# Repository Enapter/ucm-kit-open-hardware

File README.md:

# What is Enapter UCM Kit

This repository hosts Enapter UCM Kit open hardware documentation for building your own IoT edge devices. It is specially designed for makers, students and researchers to test, learn and teach IoT and Smart Energy.

Enapter UCM Kit based on several important open source and free to use components and provides full-stack IoT technology kit (hardware and software) for rapid development of connected appplications. This opens possibilities for personal technology trials and hardware prototyping. Which is extremely helpful for developing innovative cost-efficient smart energy solutions for emerging markets.

# How to Use

All schematics, CAD files and supplementary materials in this repository are subject of [Solderpad Hardware License v2.1](http://solderpad.org/licenses/SHL-2.1/). Feel free to modify and use for your own projects.

Find more information about Enapter UCM Kit at [Enapter Developer's Portal](https://go.enapter.com/ucmkit-enpkit).

# Release Notes

Check out the [Changelog](./CHANGELOG.md) for the latest updates and release notes.

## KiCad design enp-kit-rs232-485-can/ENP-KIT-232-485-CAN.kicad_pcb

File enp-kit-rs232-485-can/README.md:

## ENP-KIT-232-485-CAN

The ENP-KIT-232-485-CAN board is used for demonstrating the capabilities of the Enapter software, implements RS232, RS485, CAN interfaces.

Board was designed in an open-source EDA software <a href="https://www.kicad.org/" target="_blank">KiCad 6.0.</a>

| Description        | Resource                                                     | Note        |
| ------------------ | ------------------------------------------------------------ | ----------- |
| Production files   | [Full set of docs/files](./Production_files/ENP-KIT-232-485-CAN_V1.0.zip)| ZIP archive |
| Schematic          | [ENP-KIT-232-485-CAN](./Production_files/ENP-KIT-232-485-CAN_V1.0_schematic.pdf)  | PDF         |
| Quick Start Guide  | Coming soon... | PDF         |
| Plastic Enclosure  | <a href="https://www.budind.com/product/general-use-boxes/utilibox-style-j-series-utility-boxes/cu-1941-mb" target="_blank">CU-1941-MB</a> | Plastic box, suitable for this board |
| Where to order for production  | <a href="https://cart.jlcpcb.com/quote?orderType=1&stencilLayer=2&stencilWidth=100&stencilLength=100" target="_blank">jlcpcb.com</a> | You can order the board together with SMT Assembly, there is a separate [archive](./Production_files/jlcpcb_files_V1.0.zip) that includes everything you need |

You also need module:
ESP32-DevKitC-32D and micro USB - USB cable.

Be careful these components are not in the BOM.

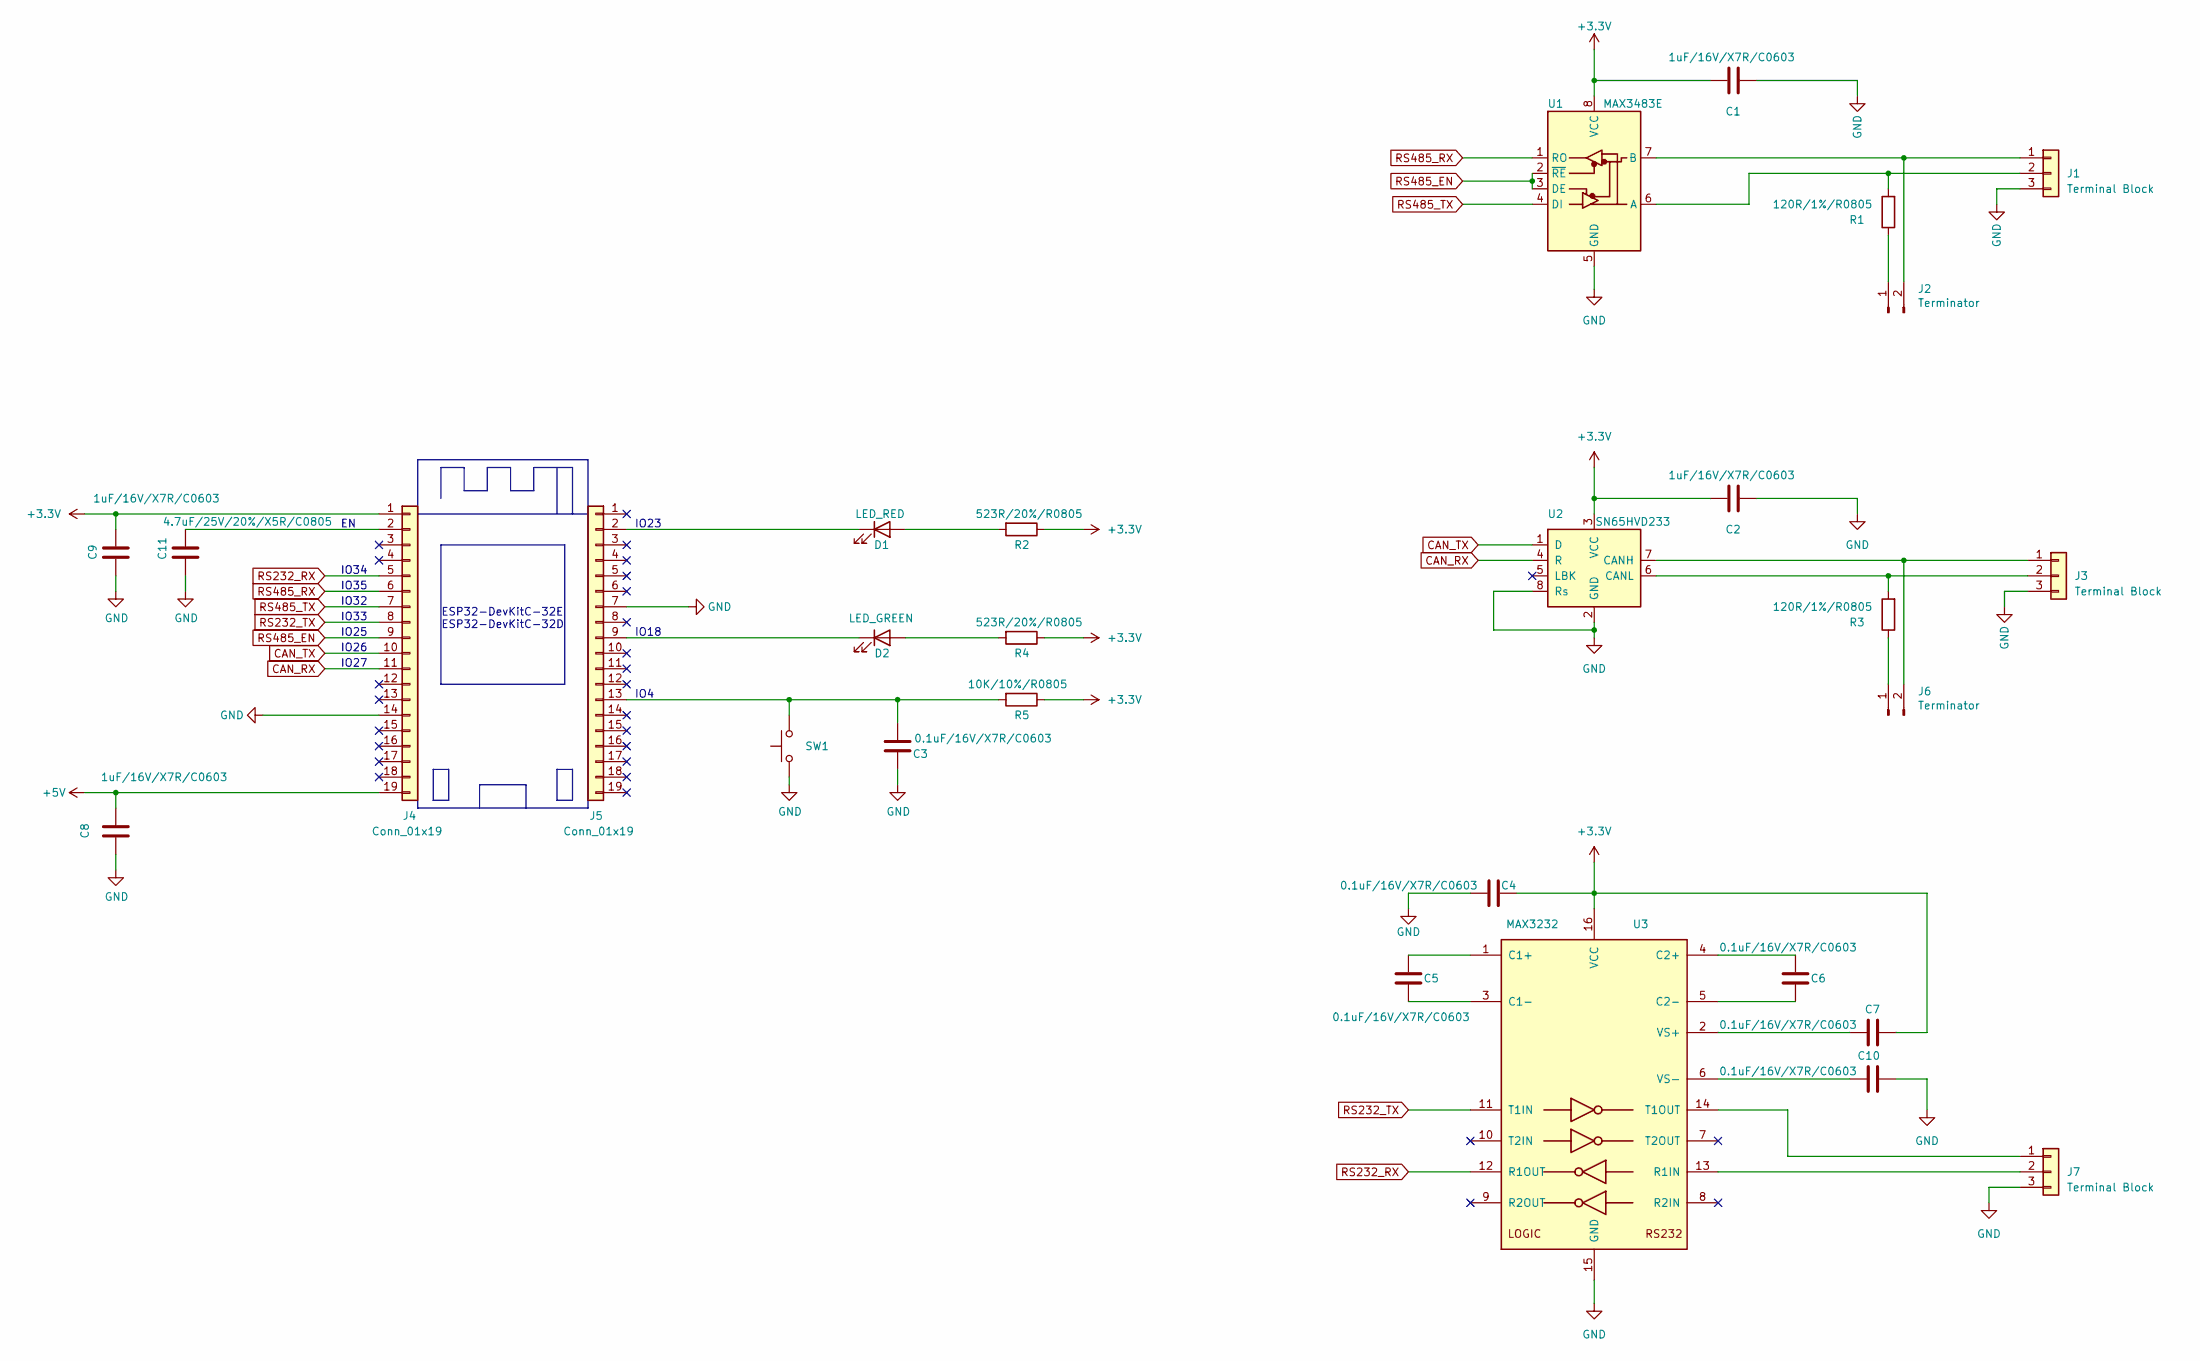
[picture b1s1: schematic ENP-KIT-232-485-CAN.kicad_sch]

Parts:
C1, C2, C8, C9: 1uF/16V/X7R/C0603; C_0603_1608Metric; Part number CL10A105KB8NNNC; JLCPCB Part # C15849
C3, C4, C5, C6, C7, C10: 0.1uF/16V/X7R/C0603; C_0603_1608Metric; Part number CC0603KRX7R9BB104; JLCPCB Part # C14663
C11: 4.7uF/25V/20%/X5R/C0805; C_0805_2012Metric; Part number CL21A475KAQNNNG; JLCPCB Part # C1779
D1: LED_RED; LED_0805_2012Metric; Part number APT2012SURC; JLCPCB Part # C84256
D2: LED_GREEN; LED_0805_2012Metric; Part number APT2012ZGC; JLCPCB Part # C2297
J1, J3, J7: Terminal Block; TerminalBlock_Phoenix_PT-1,5-3-3.5-H_1x03_P3.50mm_Horizontal; Part number DG350-3.5-03P-14-00A(H); JLCPCB Part # C2760669
J2, J6: Terminator; PinHeader_1x02_P2.54mm_Vertical; Part number DS1021-1*2SF11-B; JLCPCB Part # C492401
J4, J5: Conn_01x19; PinSocket_1x19_P2.54mm_Vertical; Part number PBS-19 (DS1023-1*19SF1); JLCPCB Part # C319202
R1, R3: 120R/1%/R0805; R_0805_2012Metric; Part number RC0805FR-07120RL; JLCPCB Part # C114245
R2, R4: 523R/20%/R0805; R_0805_2012Metric; Part number RC0805FR-07523RL; JLCPCB Part # C218615
R5: 10K/10%/R0805; R_0805_2012Metric; Part number RC0805FR-0710KL; JLCPCB Part # C17414
SW1: SW_Push; SW_Push_1P1T_NO_6x6mm_H9.5mm; Part number DTSM-62Y-V-T/R; JLCPCB Part # C2834922
U1: MAX3483E; SO-8_3.9x4.9mm_P1.27mm; Part number MAX3485EESA+; JLCPCB Part # C668204
U2: SN65HVD233; SOIC-8_3.9x4.9mm_P1.27mm; Part number SN65HVD231DR; JLCPCB Part # C129257
U3: MAX3232; SOIC-16_3.9x9.9mm_P1.27mm; Part number MAX3232ESE+; JLCPCB Part # C2904738

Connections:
+3.3V: C1.1, C2.1, C4.2, C7.2, C9.1, J4.1, R2.1, R4.1, R5.1, U1.8 (VCC), U2.3 (VCC), U3.16 (VCC)
+5V: C8.1, J4.19; also elsewhere on the board
CAN_RX: J4.11, U2.4 (R)
CAN_TX: J4.10, U2.1 (D)
GND: C1.2, C2.2, C3.1, C4.1, C8.2, C9.2, C10.2, C11.2, J1.3, J3.3, J4.14, J5.7, J7.3, SW1.1, U1.5 (GND), U2.2 (GND), U2.8 (Rs), U3.15 (GND); also elsewhere on the board
unnamed: C3.2, J5.13, R5.2, SW1.2
unnamed: C5.1, U3.3 (C1-)
unnamed: C5.2, U3.1 (C1+)
unnamed: C6.1, U3.5 (C2-)
unnamed: C6.2, U3.4 (C2+)
unnamed: C7.1, U3.2 (VS+)
unnamed: C10.1, U3.6 (VS-)
unnamed: D1.1 (K), J5.2
unnamed: D1.2 (A), R2.2
unnamed: D2.1 (K), J5.9
unnamed: D2.2 (A), R4.2
unnamed: J1.1, J2.2, U1.7 (B)
unnamed: J1.2, R1.2, U1.6 (A)
unnamed: J2.1, R1.1
unnamed: J3.1, J6.2, U2.7 (CANH)
unnamed: J3.2, R3.2, U2.6 (CANL)
unnamed: C11.1, J4.2
unnamed: J6.1, R3.1
unnamed: J7.1, U3.14 (T1OUT)
unnamed: J7.2, U3.13 (R1IN)
RS232_RX: J4.5, U3.12 (R1OUT)
RS232_TX: J4.8, U3.11 (T1IN)
RS485_EN: J4.9, U1.2 (~RE), U1.3 (DE)
RS485_RX: J4.6, U1.1 (RO)
RS485_TX: J4.7, U1.4 (DI)

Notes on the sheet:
IO4
IO35
IO26
IO27
IO18
ESP32-DevKitC-32E ESP32-DevKitC-32D
IO32
IO34
IO33
IO23
IO25

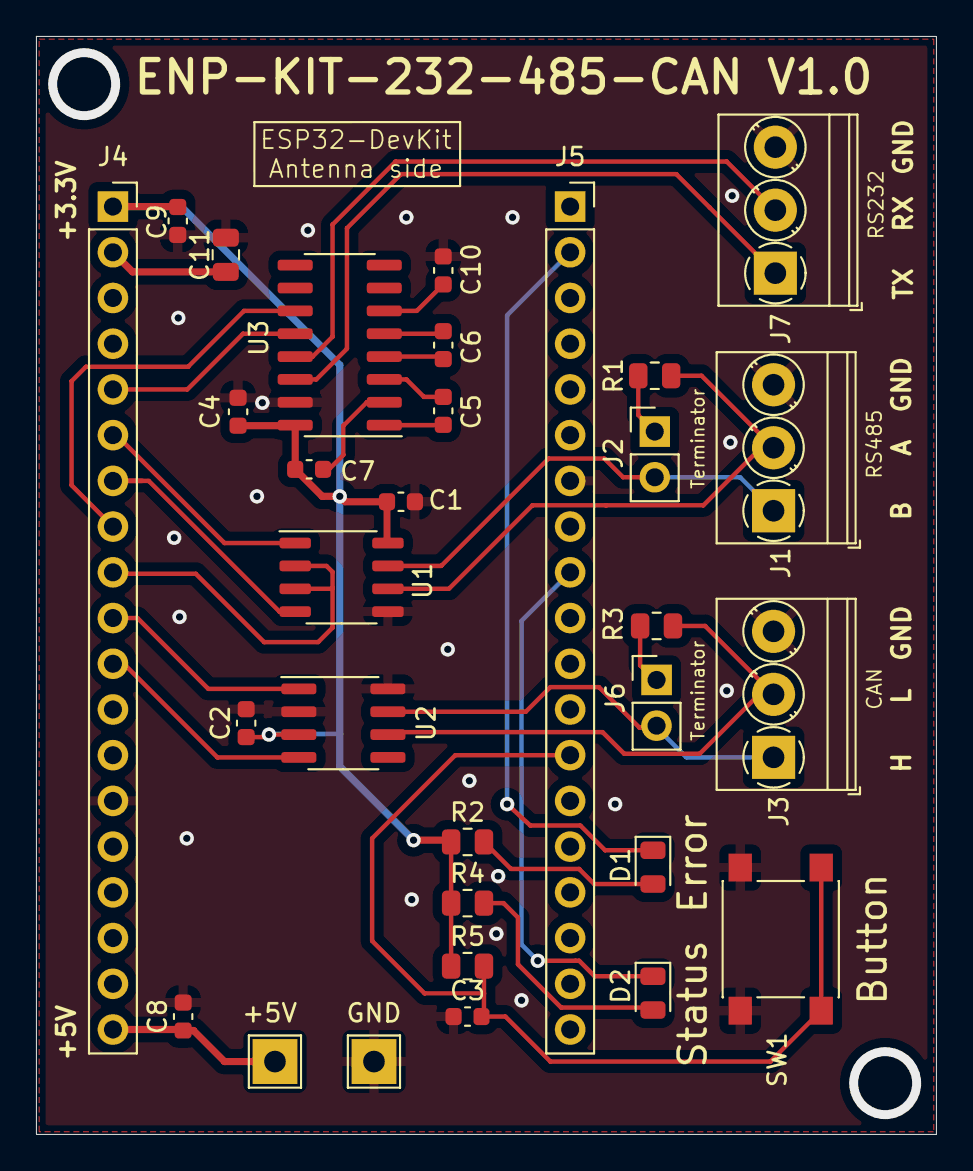
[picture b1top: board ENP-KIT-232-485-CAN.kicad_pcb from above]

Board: 2 copper layers, 50.0 x 61.0 mm, 31 parts (0 on the bottom side), 30 nets.

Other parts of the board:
+5V: TestPoint_THTPad_2.5x2.5mm_Drill1.2mm
GND: TestPoint_THTPad_2.5x2.5mm_Drill1.2mm

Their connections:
+5V: +5V.1; also elsewhere on the board
GND: GND.1; also elsewhere on the board

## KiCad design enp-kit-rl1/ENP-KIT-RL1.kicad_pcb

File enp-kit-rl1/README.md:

## ENP-KIT-RL1

The ENP-KIT-RL1 board is used for demonstrating the capabilities of the Enapter software, implements 1 channel normally open relay.

Board was designed in an open-source EDA software <a href="https://www.kicad.org/" target="_blank">KiCad 6.0.</a>

| Description        | Resource                                                     | Note        |
| ------------------ | ------------------------------------------------------------ | ----------- |
| Production files   | [Full set of docs/files](./Production_files/ENP-KIT-RL1_V1.0.zip)| ZIP archive |
| Schematic          | [ENP-KIT-RL1](./Production_files/ENP-KIT-RL1_V1.0_schematic.pdf)  | PDF         |
| Quick Start Guide  | Coming soon... | PDF         |
| Plastic Enclosure  | <a href="https://www.budind.com/product/general-use-boxes/utilibox-style-j-series-utility-boxes/cu-1941-mb" target="_blank">CU-1941-MB</a> | Plastic box, suitable for this board |
| Where to order for production  | <a href="https://cart.jlcpcb.com/quote?orderType=1&stencilLayer=2&stencilWidth=100&stencilLength=100" target="_blank">jlcpcb.com</a> | You can order the board together with SMT Assembly, there is a separate [archive](./Production_files/jlcpcb_files_V1.0.zip) that includes everything you need |

You also need module:
ESP32-DevKitC-32D and micro USB - USB cable.

Be careful these components are not in the BOM.

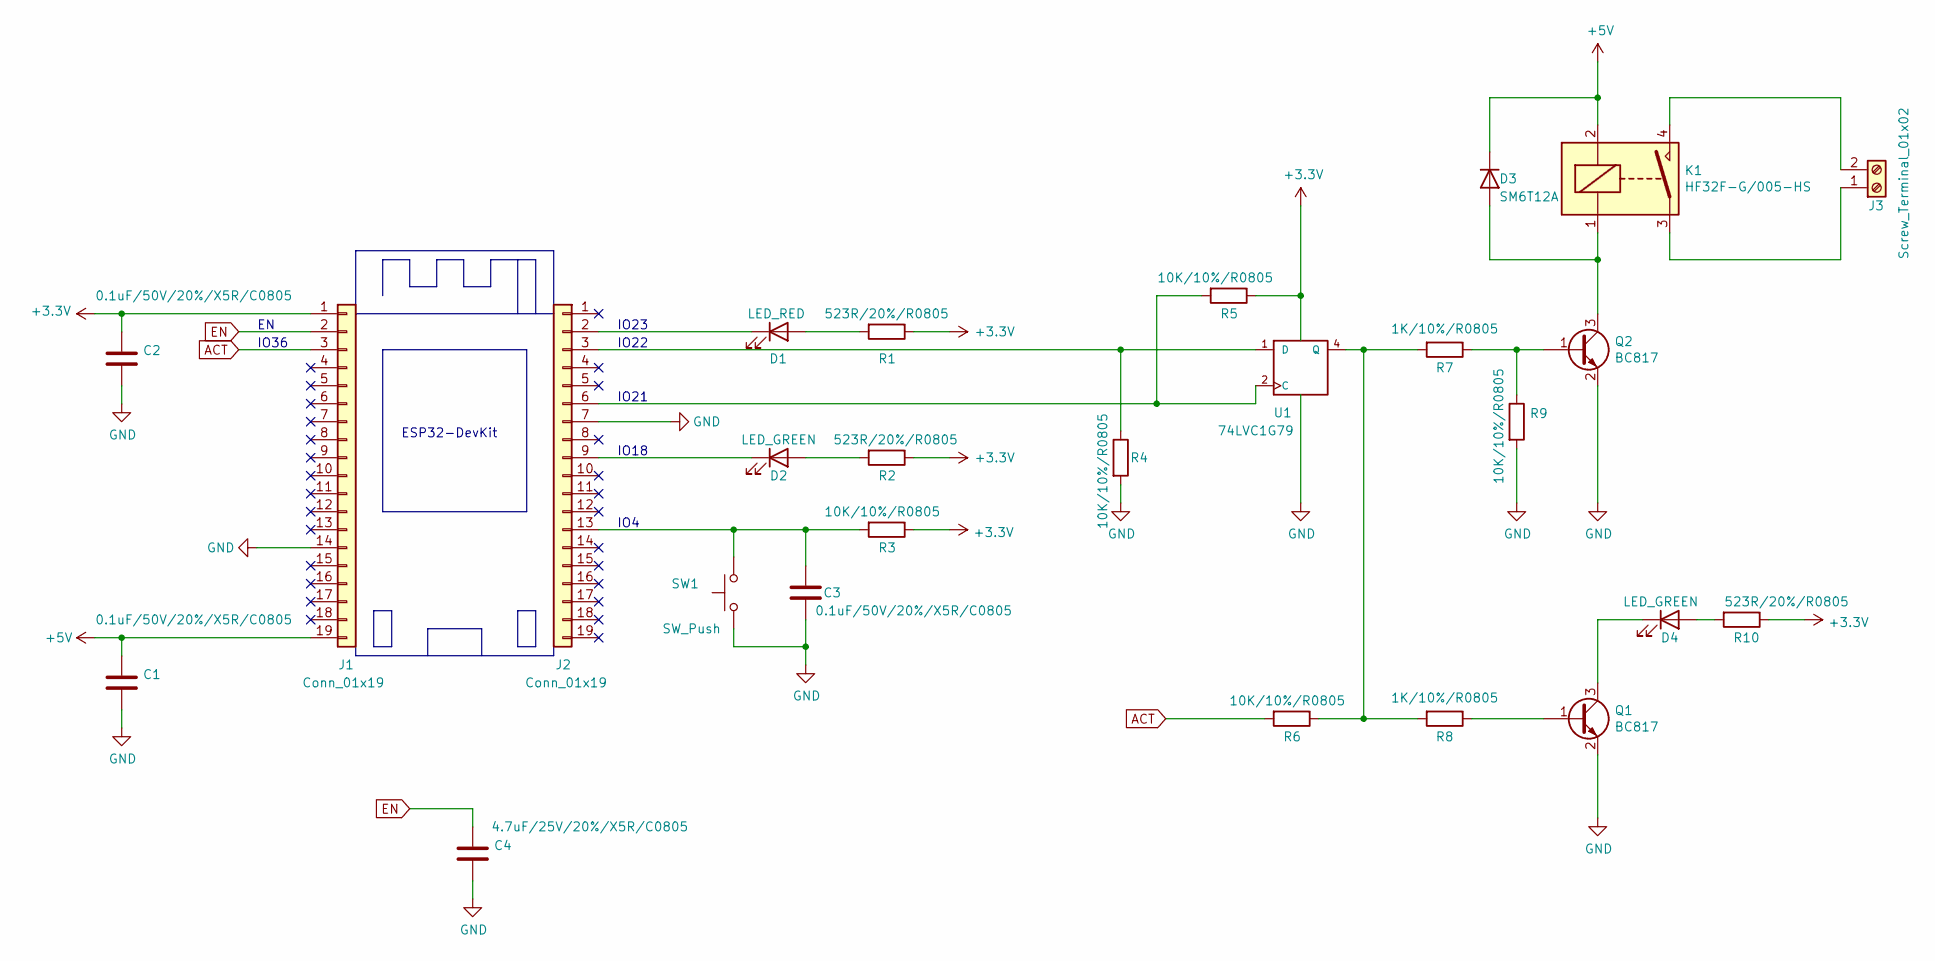
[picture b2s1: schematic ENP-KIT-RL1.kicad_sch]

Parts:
C1, C2, C3: 0.1uF/50V/20%/X5R/C0805; C_0805_2012Metric; Part number C0805C104M5RACTU; JLCPCB Part # C286511
C4: 4.7uF/25V/20%/X5R/C0805; C_0805_2012Metric; Part number CL21A475KAQNNNG; JLCPCB Part # C1779
D1: LED_RED; LED_0805_2012Metric; Part number APT2012SURC; JLCPCB Part # C84256
D2, D4: LED_GREEN; LED_0805_2012Metric; Part number APT2012ZGC; JLCPCB Part # C2297
D3: SM6T12A; D_SMB; Part number SM6T12A; JLCPCB Part # C113981
J1, J2: Conn_01x19; PinSocket_1x19_P2.54mm_Vertical; Part number PBS-19 (DS1023-1*19SF1); JLCPCB Part # C319202
J3: Screw_Terminal_01x02; TerminalBlock_Phoenix_MKDS-1,5-2-5.08_1x02_P5.08mm_Horizont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; Part number DG500-5.08-02P-14-00A(H); JLCPCB Part # C691859
K1: HF32F-G/005-HS; HF32F-G; Part number HF32F-G/005-HS; JLCPCB Part # C74541
Q1, Q2: BC817; SOT-23; Part number BC817-16,215; JLCPCB Part # C118725
R1, R2, R10: 523R/20%/R0805; R_0805_2012Metric; Part number RC0805FR-07523RL; JLCPCB Part # C218615
R3, R4, R5, R6, R9: 10K/10%/R0805; R_0805_2012Metric; Part number RC0805FR-0710KL; JLCPCB Part # C17414
R7, R8: 1K/10%/R0805; R_0805_2012Metric; Part number RC0805FR-071KL; JLCPCB Part # C269744
SW1: SW_Push; SW_Push_1P1T_NO_6x6mm_H9.5mm; Part number DTSM-62Y-V-T/R; JLCPCB Part # C2834922
U1: 74LVC1G79; SOT-23-5; Part number SN74LVC1G79DBV; JLCPCB Part # C42878

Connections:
+3V3: C2.1, J1.1, R1.1, R2.1, R3.1, R5.1, R10.1, U1.5 (VCC)
+5V: C1.1, D3.1 (K), J1.19, K1.2; also elsewhere on the board
ACT: J1.3, R6.2
EN: C4.1, J1.2
GND: C1.2, C2.2, C3.1, C4.2, J1.14, J2.7, Q1.2 (E), Q2.2 (E), R4.2, R9.2, SW1.1, U1.3 (GND); also elsewhere on the board
unnamed: C3.2, J2.13, R3.2, SW1.2
unnamed: D1.1 (K), J2.2
unnamed: D1.2 (A), R1.2
unnamed: D2.1 (K), J2.9
unnamed: D2.2 (A), R2.2
unnamed: D3.2 (A), K1.1, Q2.3 (C)
unnamed: D4.1 (K), Q1.3 (C)
unnamed: D4.2 (A), R10.2
unnamed: J2.3, R4.1, U1.1 (D)
unnamed: J2.6, R5.2, U1.2 (C)
unnamed: J3.1, K1.3
unnamed: J3.2, K1.4
unnamed: Q1.1 (B), R8.1
unnamed: Q2.1 (B), R7.1, R9.1
unnamed: R6.1, R7.2, R8.2, U1.4 (Q)

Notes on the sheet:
IO18
IO23
IO21
IO22
IO36
ESP32-DevKit
IO4

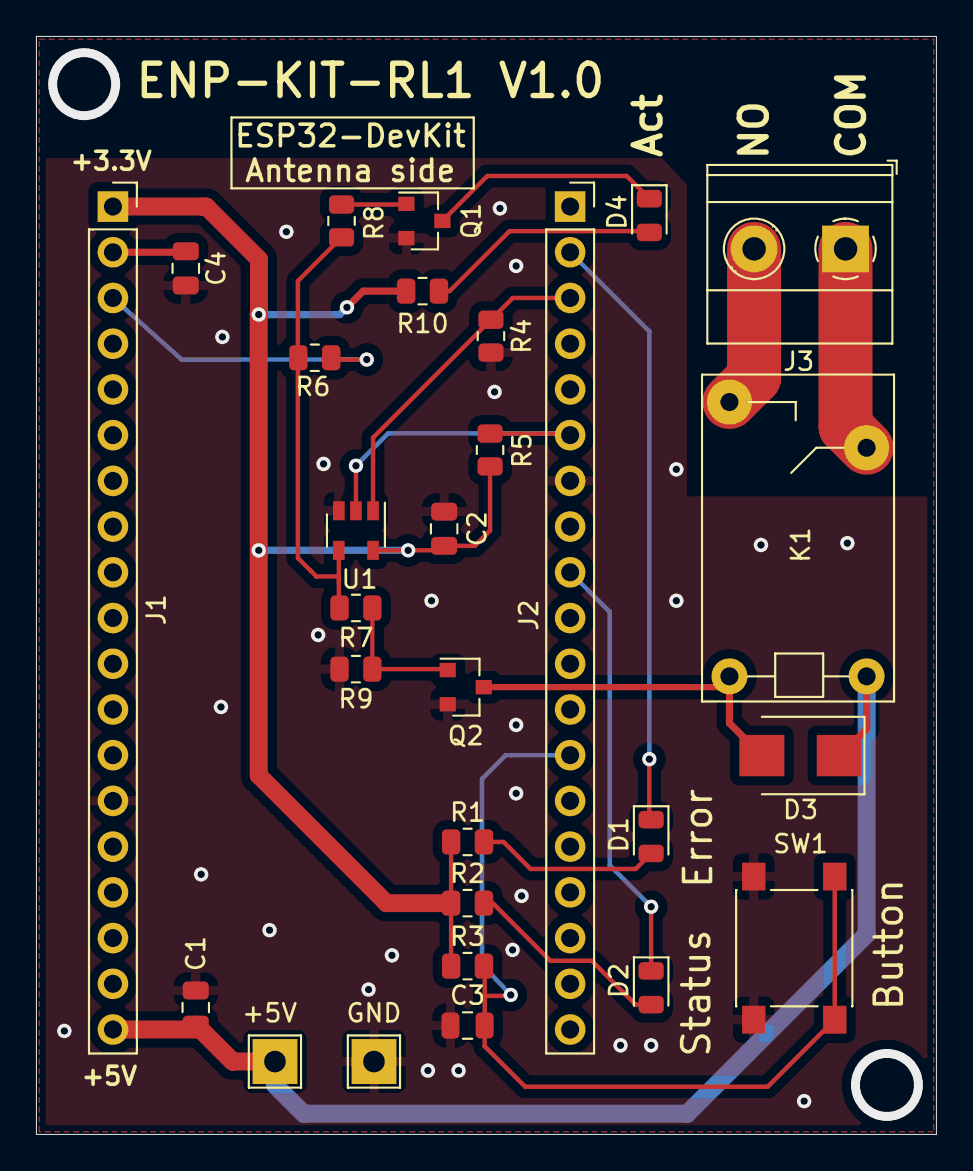
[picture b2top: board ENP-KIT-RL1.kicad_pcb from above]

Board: 2 copper layers, 50.0 x 61.0 mm, 28 parts (0 on the bottom side), 20 nets.

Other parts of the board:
+5V: TestPoint_THTPad_2.5x2.5mm_Drill1.2mm
GND: TestPoint_THTPad_2.5x2.5mm_Drill1.2mm

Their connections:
+5V: +5V.1; also elsewhere on the board
GND: GND.1; also elsewhere on the board

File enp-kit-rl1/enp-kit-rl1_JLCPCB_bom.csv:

"Comment","Designator","Footprint","JLCPCB Part #"
"0.1uF/50V/20%/X5R/C0805","C1,C2,C3","C_0805_2012Metric","C286511"
"LED_GREEN","D2,D4","LED_0805_2012Metric","C2297"
"LED_RED","D1","LED_0805_2012Metric","C84256"
"SM6T12A","D3","D_SMB","C718481"
"Conn_01x19","J1,J2","PinSocket_1x19_P2.54mm_Vertical","C319202"
"Screw_Terminal_01x02","J3","TerminalBlock_Phoenix_MKDS-1,5-2-5.08_1x02_P5.08mm_Horizontal","C691859"
"HF32F-G/005-HS","K1","HF32F-G","C74541"
"BC817","Q1,Q2","SOT-23","C118725"
"10K/10%/R0805","R3,R4,R5,R6,R9","R_0805_2012Metric","C17414"
"1K/10%/R0805","R7,R8","R_0805_2012Metric","C269744"
"523R/20%/R0805","R1,R2,R10","R_0805_2012Metric","C218615"
"SW_Push","SW1","SW_Push_1P1T_NO_6x6mm_H9.5mm","C2834922"
"74LVC1G79","U1","SOT-23-5","C42878"

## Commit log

2022-11-01 ENP-KIT-RL1 initial commit
2022-11-02 Create LICENSE
2022-11-22 UCM kit rl1 refactor
2022-11-28 add kicad project sources
2022-11-28 fix readme
2022-11-28 remove html bom section
2022-11-29 change pic
2022-11-30 adding documentation and LICENSE
2022-12-01 add enp-serial kit
2023-04-05 Assets folder
    Added
2023-04-05 Images and minor test improvements in Readme
    Some new headers and dark/light image placeholders.
2023-04-05 Images for readme
    Dark/light
2023-04-07 Readme images updated
2023-04-07 Images update
2023-06-28 fixing image for the light theme
2023-06-28 changin light image
2024-01-08 add changelog
